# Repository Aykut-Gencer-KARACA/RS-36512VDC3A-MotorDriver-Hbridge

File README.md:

<div align="center">

<br/>

<br/><br/>

**Mikrodenetleyicisiz, tamamen analog PWM ile çalışan çift yönlü motor sürücü.**<br/>
24 V girişten 12.3 V motor barası üretir; hızı bir trimpotla, yönü bir anahtarla ayarlanır.

</div>

## İçindekiler

- [Genel bakış](#-genel-bakış)
- [Öne çıkanlar](#-öne-çıkanlar)
- [Sistem mimarisi](#-sistem-mimarisi)
- [Çalışma prensibi](#-çalışma-prensibi)
- [Donanım](#-donanım)
- [Tasarım hesapları](#-tasarım-hesapları)
- [Şematik](#-şematik)
- [PCB](#-pcb)
- [Malzeme listesi](#-malzeme-listesi)
- [Depo yapısı](#-depo-yapısı)

## ◆ Genel bakış

Bu proje, bir önceki çalışmamda kullandığım **RS-365 serisi 12 V DC / 3 A** motoru **çift yönlü** ve **hız kontrollü** sürmek için tasarlanmış bir H-köprü kartıdır. Güç tarafında 24 V DC girişten **LM2596S-ADJ** ile 12.3 V'luk motor barası üretilir. PWM sinyali mikrodenetleyici olmadan **LM555** ile, yön kararı **CD4081 / CD4069** mantık kapılarıyla verilir; köprüyü iki adet **EG4427** gate sürücü besler.

| Özellik | Değer |
|---|---|
| **Giriş** | 24 V DC · vida klemens (J1) · 2.5 A sigorta (F1) |
| **Motor barası** | 12.3 V · LM2596S-ADJ, R10 1 kΩ / R11 9 kΩ geri besleme |
| **Motor** | RS-365 · 12 V DC · 3 A |
| **Regülatör** | L1 68 µH (ISAT 4.5 A) · D6 4 A Schottky · çıkışta C8, C9 470 µF 35 V |
| **PWM** | LM555 astable · C15 6.8 nF · hesaplanan ≈ 16 kHz · duty ≈ %15 – %92 |
| **Hız ayarı** | RV1 10 kΩ multiturn trimpot |
| **Yön** | SW1 SPDT, orta konumda dur · CD4081 (AND) + CD4069 (NOT) |
| **Gate sürücü** | 2 × EG4427 · MOSFET başına 100 Ω gate direnci |
| **Köprü** | Q2, Q4 P-kanal (üst) · Q3, Q5 N-kanal (alt) · TO-220 · her birine paralel 4 A Schottky |
| **Kart** | 115.65 × 44.48 mm · 4 katmanlı · 1.6 mm |

## ◆ Öne çıkanlar

<table>
<tr>
<td width="50%" valign="top">

**Tamamen analog PWM**<br/>
Frekans ve duty bir LM555 ile üretilir. İki diyot şarj ve deşarj yollarını ayırdığı için trimpot yalnızca duty'yi değiştirir; toplam direnç sabit kaldığından frekans yaklaşık sabittir.

</td>
<td width="50%" valign="top">

**Giriş koruması**<br/>
2.5 A sigorta, P-kanal giriş MOSFET'i (Q1) ve gate'i 12 V zener (D1) ile sınırlanmış koruma devresi. Sigorta 24 V tarafında olduğu için 3 A motor akımı, giriş tarafında yaklaşık 1.8 A'e karşılık gelir (%85 verim varsayımıyla).

</td>
</tr>
<tr>
<td valign="top">

**Gate sürücü ile hızlı anahtarlama**<br/>
Mantık kapıları gate'i doğrudan sürecek akımı veremez. İki EG4427, gate'leri 100 Ω dirençler üzerinden besler; her MOSFET'te 10 kΩ pull-up / pull-down açılış anında gate'i kapalı tutar.

</td>
<td valign="top">

**Her MOSFET'e Schottky diyot**<br/>
D2 – D5 (4 A, SMC), PWM kapalıyken motor akımının dolaşacağı yolu açar ve MOSFET gövde diyotlarını rahatlatır.

</td>
</tr>
</table>

## ◆ Sistem mimarisi

Güç yolu soldan sağa akıyor: 24 V giriş sigortadan, giriş koruma devresinden (Q1, D1) ve LM2596'dan geçip 12.3 V'luk `V_MOTOR` barasına ulaşıyor. Bu baradan iki kol ayrılıyor:

- **Mantık beslemesi** · 10 Ω (R12) ve 470 µF (C11) ile süzülerek LM555, CD4081, CD4069 ve EG4427'leri besler (kesim frekansı ≈ 34 Hz).
- **H-köprü** · MOSFET'ler ve motor doğrudan bu baradan beslenir.

PWM, yön bilgisiyle kapılarda birleştirilir; EG4427'ler sinyali güçlendirip köprünün dört MOSFET'ine iletir.

## ◆ Çalışma prensibi

Köprünün her bacağında bir P-kanal (üst) ve bir N-kanal (alt) MOSFET vardır; motor iki bacağın orta noktaları arasına bağlanır.

- **İleri:** Q2 sabit iletimde, Q5 PWM ile anahtarlanır. Akım `V_MOTOR → Q2 → motor → Q5 → GND` yolunu izler.
- **Geri:** Q4 sabit iletimde, Q3 PWM ile anahtarlanır. Akım motordan ters yönde geçer.
- **Dur:** SW1 orta konumdayken tüm çıkışlar pasiftir.
- **Hız:** Motora uygulanan ortalama gerilim $V_{ort} \approx D \times 12.3\text{ V}$ olur; RV1 duty'yi değiştirir.

Üst kolda P-kanal MOSFET'ler kullanılmıştır: gate'e GND yakın bir gerilim verildiğinde açılırlar, gate'leri pull-up dirençleriyle motor barasına bağlı olduğundan boşta kapalı kalırlar ve böylece üst kol için ayrıca bir bootstrap devresi gerekmez.

## ◆ Donanım

<details open>
<summary><b>Güç girişi ve regülatör</b></summary>
<br/>

| Blok | Parça | Not |
|---|---|---|
| Giriş | J1 vida klemens (MX126-5.0-02P, C5188434; 5.00 mm, 10 A, 300 V) · F1 2010T2.5A250V (C354903; 2.5 A, 300 V DC) | Sigorta 24 V tarafında |
| Giriş koruma MOSFET'i | Q1 (P-kanal, TO-220) · R2 10 kΩ · D1 ZMM12V (C5345999; 11.4 – 12.7 V, 500 mW) | Gate R2 ile GND'ye çekili, zener V<sub>GS</sub>'i sınırlar |
| Regülatör | U3 LM2596S-ADJ | R10 1 kΩ / R11 9 kΩ → 12.3 V |
| Bobin | L1 SMMS0865-680MT · 68 µH (C42443515) | ISAT 4.5 A · Irms 4 A · DCR 180 mΩ · 9 × 8.1 mm |
| Diyot | D6 4 A Schottky (SMC) | Serbest dolaşım |
| Giriş kondansatörleri | C1, C2 470 µF 35 V (şematik değeri) · C4 1 µF | Anahtarlama anındaki ani akımı karşılar. Kütüphane kaydı (LCSC C335982) ROQANG RVT1A471M0607 = 470 µF / **10 V**, 6.3 × 7.7 mm'dir |
| Çıkış kondansatörleri | C8, C9 470 µF 35 V (şematik değeri) · C10 1 µF | Hızlı tepki için seramik, süreğen düşüşler için polarize; C8 / C9 için de aynı kütüphane parçası (10 V) geçerlidir |

</details>

<details>
<summary><b>PWM üretimi — LM555</b></summary>
<br/>

- Astable modda çalışır; C15 = 6.8 nF kondansatör Vcc'nin 1/3 ile 2/3'ü arasında şarj/deşarj olur.
- D7 ve D8 diyotları şarj ve deşarj akımlarını RV1'in iki farklı yarısından geçirir. Şarj yolu: `R16 + RV1(üst) + R15`, deşarj yolu: `RV1(alt) + R15`.
- Toplam direnç RV1'in konumundan bağımsızdır; bu yüzden frekans sabit kalır, yalnızca duty değişir.
- C13 ve C14 besleme / kontrol pini dekuplaj kondansatörleridir.

</details>

<details>
<summary><b>Karar birimi — SW1, CD4081, CD4069</b></summary>
<br/>

- SW1 üç konumlu (orta konumda OFF) bir SPDT anahtardır; seçilen yön hattı 12 V'a çekilirken diğeri R13 / R14 (10 kΩ) ile GND'de tutulur.
- **CD4081** (dörtlü AND) yön bilgisini LM555 PWM çıkışıyla birleştirir.
- **CD4069** (altılı NOT) yön hatlarını tersleyerek üst kol P-kanal MOSFET'lerin (Q2, Q4) gate sinyalini üretir; CD4081 çıkışları ise alt kol (Q3, Q5) sürücüsüne gider.
- Mantık beslemesi (`IC_Input`) 10 Ω + 470 µF ile süzülen 12.3 V barasından gelir; 4000 serisi CMOS bu gerilimde çalışır.

</details>

<details>
<summary><b>Gate sürücü — EG4427</b></summary>
<br/>

- İki entegre, dört MOSFET gate'ini sürer (INA / INB → OUTA / OUTB).
- Her entegrenin beslemesinde 4.7 µF + 100 nF bulunur.
- Çıkışlar 100 Ω (R3, R4, R7, R8) gate dirençleriyle MOSFET'lere gider.
- Üst kol gate'leri 10 kΩ (R1, R9) ile motor barasına, alt kol gate'leri 10 kΩ (R5, R6) ile GND'ye bağlıdır.

</details>

<details>
<summary><b>Motor köprüsü</b></summary>
<br/>

| Ref | Tür | Görev |
|---|---|---|
| Q2, Q4 | P-kanal, TO-220 | Üst kol, yön seçimi |
| Q3, Q5 | N-kanal, TO-220 | Alt kol, PWM |
| D2 – D5 | 4 A Schottky, SMC | Her MOSFET'e paralel serbest dolaşım diyodu |
| M1 | Vida klemens | Motor bağlantısı |

</details>

## ◆ Tasarım hesapları

> Değerler KiCad şematik / PCB dosyalarından (RevA), TI LM2596 (SNVS124G) ve LM555 (SNAS548D) datasheet'lerinden ve EG4427'nin LCSC ürün sayfasından alınmıştır. MOSFET'lerin parça numarası şematikte yazılı olmadığı için MOSFET hesapları gereksinim düzeyindedir; datasheet'te karşılığı olmayan değerler "varsayım" diye işaretlenmiştir.

<details>
<summary><b>Giriş akımı ve sigorta</b></summary>
<br/>

$$P_{OUT} = 12.3\text{ V} \times 3\text{ A} = 36.9\text{ W} \quad\Rightarrow\quad I_{IN} = \frac{36.9\text{ W}}{\eta \times 24\text{ V}} = 1.71\text{ A}\ (\eta = 0.90),\quad 1.81\text{ A}\ (\eta = 0.85)$$

η = %90, LM2596 datasheet'inin 25 V → 12 V, 3 A noktasındaki tipik verimidir (7.7). 2.5 A sigorta bu akımın ≈ 1.4 katıdır; sigortanın sürekli akımda anma değerinin %75'inde (1.9 A) çalıştırılması kuralıyla 1.7 – 1.8 A sınırın içindedir. Motorun kalkış / sıkışma akımı 3 A'i belirgin aşarsa sigorta ve LM2596'nın akım sınırı devreye girer (rotor kilitli akımı bu belgede verilmemiştir).

</details>

<details>
<summary><b>Giriş koruma devresi (Q1, D1, R2)</b></summary>
<br/>

Q1'in gate'i R2 (10 kΩ) ile GND'ye çekilidir; D1 (12 V zener) gate ile drain arasında, gate gerilimini drain gerilimine göre en fazla 12 V aşağıda tutar:

$$V_{GS} \approx -12\text{ V}\ (\text{iletimde}), \qquad I_{R2} = \frac{24 - 12}{10\text{ k}\Omega} = 1.2\text{ mA}, \qquad P_{R2} = P_{D1} = 12\text{ V} \times 1.2\text{ mA} = 14.4\text{ mW}$$

R2 için bu, 0805'in 125 mW değerinin %12'sidir. Q1 üzerindeki iletim kaybı $P = I_{IN}^2 R_{DS(on)}$: 1.8 A ve 50 mΩ için 0.16 W. Q1 için $V_{DS} \ge 40\text{ V}$ (60 V önerilir) gerekir. Başlangıçta drain 0 V iken gate geçici olarak 0 V'ta kaldığından $V_{GS}$ kısa süreliğine −24 V'a ulaşır (zener drain 12 V'u aştıktan sonra iletime geçer); bu nedenle gate–source sınırı ±20 V'tan yüksek bir parça tercih edilmelidir.

**Giriş kondansatörleri (C1, C2):** toplam 940 µF; depolanan enerji $\tfrac{1}{2} C V^2 = \tfrac{1}{2} \cdot 940\ \mu\text{F} \cdot 24^2 = 0.27\text{ J}$. LM2596 datasheet'i RMS akımın $\ge I_{LOAD}/2 = 1.5\text{ A}$ (iki kondansatör için her biri ≥ 0.75 A) ve gerilim değerinin $\approx 1.5 \times V_{IN} = 36\text{ V}$ olmasını ister (9.2.2.2.6); 35 V'luk kondansatör 24 V'ta gerilim değerinin %69'unda çalışır.

**Parça doğrulaması (C1, C2, C8, C9):** şematik değeri 470 µF / 35 V'tur, ancak footprint ve 3B model kütüphanedeki LCSC C335982 kaydından gelir: ROQANG RVT1A471M0607, **470 µF / 10 V**, 6.3 × 7.7 mm, dalgalanma akımı 200 mA @ 120 Hz. 6.3 mm gövdeli SMD kutuda 470 µF yalnızca 6.3 – 10 V'ta bulunur; 470 µF / 35 V standart alüminyum elektrolitikte ≈ 10 × 10 mm veya daha büyük kutu gerektirir. 10 V'luk bu parça 24 V (C1, C2) ve 12.3 V (C8, C9) baralarında kullanılamaz. Ayrıca LM2596 girişindeki RMS akım $I_{RMS} = I_{LOAD}\sqrt{D(1-D)} = 3\sqrt{0.548 \cdot 0.452} = 1.49\text{ A}$'dir; iki kondansatörün toplam 0.4 A'lik dalgalanma akımı bunun çok altındadır. 35 V'luk gerçek kondansatörler için footprint değiştirilmelidir.

**C11 (470 µF / 50 V):** footprint 0603 (1.6 × 0.8 mm) olarak atanmıştır; bu değerde bir kondansatör 0603 kılıfta bulunmaz, footprint gerçek parçaya göre düzeltilmelidir.

</details>

<details>
<summary><b>Çıkış gerilimi (12.3 V)</b></summary>
<br/>

$$V_{OUT} = V_{REF} \times \left(1 + \frac{R_{11}}{R_{10}}\right) = 1.23\text{ V} \times \left(1 + \frac{9\text{ k}\Omega}{1\text{ k}\Omega}\right) = 12.3\text{ V}$$

R10 = 1 kΩ, datasheet'in 240 Ω – 1.5 kΩ aralığındadır. Referans toleransıyla (1.193 – 1.267 V) çıkış 11.93 – 12.67 V arasında olabilir (≈ ±%3).

</details>

<details>
<summary><b>Bobin akımı ve akım sınırı</b></summary>
<br/>

Datasheet'in duty ifadesi (Denklem 8; $V_{SAT} = 1.16\text{ V}$, $V_D = 0.5\text{ V}$), 150 kHz ve $L = 68\ \mu\text{H}$ için:

$$D = \frac{12.3 + 0.5}{24 - 1.16 + 0.5} = 0.548, \qquad \Delta I_L = \frac{(24 - 1.16 - 12.3) \times 0.548}{150\text{ kHz} \times 68\ \mu\text{H}} = 0.57\text{ A}$$

$$I_{pk} = 3 + \frac{0.57}{2} = 3.28\text{ A}, \qquad E \cdot T = 38.5\text{ V}\cdot\mu\text{s}$$

Tepe akım, bobinin ISAT değerinin (4.5 A) %73'üdür.

Yük akımı $\Delta I_L / 2 = 0.28\text{ A}$'in altına düşerse regülatör süreksiz moda geçer. LM2596'nın akım sınırı tipik 4.5 A, en az 3.6 A olduğundan sürekli ortalama yük akımı üst sınırı $I_{CL} - \Delta I_L/2 = 3.3\text{ A}$ (en kötü) – 4.2 A (tipik) olur.

</details>

<details>
<summary><b>Serbest dolaşım diyodu (D6) ve çıkış kondansatörleri</b></summary>
<br/>

D6 için datasheet kuralları (9.2.2.2.5): akım ≥ 1.3 × 3 A = 3.9 A (4 A'lik diyot sağlar), ters gerilim ≥ 1.25 × 24 V = 30 V (şematikte yalnızca "4A Schottky" yazılıdır). Normal çalışmada $I_D = 3 \times (1 - 0.548) = 1.35\text{ A}$, $P_D = 0.5 \times 1.35 = 0.68\text{ W}$.

Çıkış kondansatörü için datasheet 82 – 820 µF aralığını ve $\ge 1.5 \times V_{OUT}$ gerilimi ister (9.2.2.2.3). Kartta C8 + C9 = 940 µF'tır (35 V, 18.5 V kuralını sağlar) ve ayrıca R12 üzerinden C11 (470 µF) bağlıdır:

$$f_0 = \frac{1}{2\pi\sqrt{68\ \mu\text{H} \times 940\ \mu\text{F}}} \approx 630\text{ Hz}$$

Çıkış 10 V'un üzerinde olduğundan datasheet $C_{FF} = 1/(31 \cdot 10^3 \cdot R_{11}) \approx 3.6\text{ nF}$ önerir (Tablo 9-6: 12 V için 1 nF); kartta yoktur.

</details>

<details>
<summary><b>LM2596 güç kaybı ve ısıl kontrol</b></summary>
<br/>

İletim modeli: $P_{IC} = 1.16 \times 3 \times 0.548 + 24 \times 5\text{ mA} = 2.03\text{ W}$. Bütçe yöntemi: datasheet'in tipik %90 verimiyle toplam kayıp $36.9 / 0.9 - 36.9 = 4.1\text{ W}$; D6'nın 0.68 W'ı ve L1'in bakır kaybı $I^2 \times DCR = 3^2 \times 0.18\ \Omega = 1.62\text{ W}$ (SMMS0865-680MT, DCR 180 mΩ; LCSC C42443515) düşülürse entegreye $4.1 - 0.68 - 1.62 = 1.80\text{ W}$ kalır; iki yöntem birbirine yakındır. Kart alanı $115.65 \times 44.48 = 5144\text{ mm}^2 \approx 7.97\text{ in}^2$ (4 katman); R<sub>θJA</sub>'nın 20 – 30 °C/W olacağı varsayıldı (datasheet 7.4: 3 in² çift yüzlü → 20, 2.5 in² tek yüzlü → 30 °C/W):

| P<sub>IC</sub> | R<sub>θJA</sub> = 20 °C/W | R<sub>θJA</sub> = 30 °C/W |
|---|---|---|
| 1.80 W (bütçe) | T<sub>J</sub> = 76 °C | T<sub>J</sub> = 94 °C |
| 2.03 W (iletim modeli) | T<sub>J</sub> = 81 °C | T<sub>J</sub> = 101 °C |

İşletme sıcaklığı üst sınırı 125 °C'dir (7.3); her iki yöntemde de ≤ 101 °C'tir. L1 bobininin tam yükteki 1.62 W'lık kaybı (Irms 4 A, sınırın %75'inde çalışır) ayrıca karta ısı verir.

</details>

<details>
<summary><b>PWM frekansı ve duty aralığı (LM555)</b></summary>
<br/>

D7 / D8 şarj ve deşarj yollarını ayırır: şarj $R_{16} + R_a + R_{15}$, deşarj $R_b + R_{15}$ üzerinden ($R_a + R_b = R_{RV1} = 10\text{ k}\Omega$). Datasheet formülleri (7.4.2):

$$t_H = 0.693\,(R_{16} + R_a + R_{15})\,C_{15}, \qquad t_L = 0.693\,(R_b + R_{15})\,C_{15}$$

$$T = 0.693\,(R_{16} + R_{RV1} + 2R_{15})\,C_{15} = 0.693 \times 13\text{ k}\Omega \times 6.8\text{ nF} = 61.3\ \mu\text{s} \;\Rightarrow\; f \approx 16.3\text{ kHz}$$

$$D_{min} = \frac{R_{16} + R_{15}}{R_{16} + R_{RV1} + 2R_{15}} = \frac{2}{13} = 15\%, \qquad D_{max} = \frac{12}{13} = 92\%$$

Frekans RV1'in konumundan bağımsızdır. Diyot düşümü ($V_F = 0.6\text{ V}$, varsayım) dahil edildiğinde ($V_{CC} = 12.3\text{ V}$; kondansatör $V_{CC}/3$ ile $2V_{CC}/3$ arasında):

| R<sub>a</sub> | 0 | 2.5 kΩ | 5 kΩ | 7.5 kΩ | 10 kΩ |
|---|---|---|---|---|---|
| D (ideal) | %15 | %35 | %54 | %73 | %92 |
| f (V<sub>F</sub> = 0.6 V) | 17.4 kHz | 16.7 kHz | 16.0 kHz | 15.4 kHz | 14.8 kHz |
| D (V<sub>F</sub> = 0.6 V) | %18 | %40 | %59 | %77 | %94 |

LM555 astable başlangıç doğruluğu %2.25'tir (6.5). Deşarj sırasında pin 7 yaklaşık 0.15 V'a iner ve R16'dan $(12.3 - 0.15)/1\text{ k}\Omega = 12.2\text{ mA}$ akar (anlık 148 mW); ortalama güç $148\text{ mW} \times (1 - D)$: D ≈ %18'de 121 mW, D ≈ %94'te 9 mW. 0805 direncin anma gücü 125 mW'tır, yani en düşük duty'de R16 anma gücünün %97'sini harcar.

</details>

<details>
<summary><b>Motora uygulanan ortalama gerilim</b></summary>
<br/>

$$V_{avg} \approx D \times 12.3\text{ V}:\qquad D = 15\% \Rightarrow 1.8\text{ V},\quad 25\% \Rightarrow 3.1\text{ V},\quad 50\% \Rightarrow 6.2\text{ V},\quad 75\% \Rightarrow 9.2\text{ V},\quad 92\% \Rightarrow 11.3\text{ V}$$

</details>

<details>
<summary><b>Mantık beslemesi filtresi</b></summary>
<br/>

$$f_c = \frac{1}{2\pi \times R_{12} \times C_{11}} = \frac{1}{2\pi \times 10\ \Omega \times 470\ \mu\text{F}} \approx 34\text{ Hz}$$

Besleme akımı yaklaşık 17 – 20 mA'dir (LM555 ≈ 8 mA, R16 ortalama ≈ 6 mA, pull-up / pull-down'lar 1 – 2.5 mA, gate akımları); R12 üzerindeki düşüm en fazla $20\text{ mA} \times 10\ \Omega = 0.2\text{ V}$'tur ve mantık beslemesi ≈ 12.1 V olur. LM555 için önerilen aralık 4.5 – 16 V'tur.

</details>

<details>
<summary><b>Gate sürücü (EG4427)</b></summary>
<br/>

EG4427 (LCSC C2929102): 3 – 20 V besleme, 1.5 A tepe akım, t<sub>pHL</sub> = 60 ns / t<sub>pLH</sub> = 80 ns. Gate dirençleri 100 Ω olduğundan:

$$I_{pk} = \frac{V_{DD}}{R_g} = \frac{12.3\text{ V}}{100\ \Omega} = 123\text{ mA} \ll 1.5\text{ A}, \qquad R_{g,min} = \frac{12.3\text{ V}}{1.5\text{ A}} = 8.2\ \Omega$$

Gate dolma süresi $t \approx Q_g / I_{pk}$ ve ortalama gate gücü $P = Q_g V_{DD} f$ ($f = 16.3\text{ kHz}$; Q<sub>g</sub> örnek değerlerdir):

| Q<sub>g</sub> (örnek) | 20 nC | 40 nC | 60 nC |
|---|---|---|---|
| Dolma süresi | 163 ns | 325 ns | 488 ns |
| Ortalama gate gücü | 4.0 mW | 8.0 mW | 12.0 mW |

Hepsi 61 µs'lik PWM periyodunun %1'inden küçüktür. 4.7 µF besleme kondansatöründe bir anahtarlamada gerilim düşümü $40\text{ nC} / 4.7\ \mu\text{F} = 8.5\text{ mV}$'tur. 10 kΩ pull-up / pull-down'lardan iletimdeki bir gate için $12.3 / 10\text{ k}\Omega = 1.23\text{ mA}$ akar.

**Sürücü etkinleştirme ve mantık seviyeleri.** EG4427'nin 8 numaralı pini SD (shutdown) girişidir ve aktif-yüksektir (LCSC / EGmicro: "SD high disables outputs"; dahili 100 kΩ pull-down). Kartta SD pini GND'ye bağlıdır, yani sürücüler etkindir. Giriş eşikleri $V_{IH} = 2.5\text{ V}$, $V_{IL} = 1\text{ V}$'tur. CD4081BE (HGSEMI, C507156) ve CD4069 (Slkor, C3041279) 3 – 15 V aralığında çalışır; 12.1 V beslemede CMOS giriş eşiği $V_{IH} \approx 8.7\text{ V}$ (10 V'ta 7 V, 15 V'ta 11 V arasında doğrusal). LM555 çıkışı 100 mA'de en az $V_{CC} - 2.25\text{ V} \approx 9.9\text{ V}$ verdiğinden (CMOS yükünde daha yüksektir) gürültü payı ≥ 1.2 V'tur; LM555 alçak çıkışı ≤ 0.25 V'tur.

</details>

<details>
<summary><b>MOSFET ve Schottky diyot gereksinimleri</b></summary>
<br/>

| Parametre | Gereksinim | Hesap |
|---|---|---|
| V<sub>DS</sub> (Q2 – Q5) | ≥ 30 V | $2 \times 12.3\text{ V} \approx 25\text{ V}$ |
| V<sub>DS</sub> (Q1) | ≥ 40 V (60 V önerilir) | 24 V giriş + sıçramalar |
| I<sub>D</sub> | ≥ 9 A | $3 \times 3\text{ A}$ (ön eleme) |
| R<sub>DS(on)</sub> @ 12 V | ≤ 100 mΩ | 3 A'de $I^2 R \le 0.9\text{ W}$ |
| V<sub>GS(th)</sub> | ≤ 4 V | 12 V sürüşte tam iletim |

3 A'de iletim kaybı 30 mΩ için 0.27 W, 50 mΩ için 0.45 W, 100 mΩ için 0.90 W'tır; alt kolda PWM olduğundan ortalama kayıp D katıdır. D2 – D5 serbest dolaşım diyotlarının kaybı $P = V_F\,I\,(1 - D)$ ($V_F = 0.5\text{ V}$, 3 A varsayımı): D = %15'te 1.28 W, %50'de 0.75 W, %92'de 0.12 W.

</details>

## ◆ Şematik

Şematik beş bölüme ayrılmıştır: 24 V → 12 V regülatör, LM555 zamanlayıcı, karar birimi, gate sürücüler ve motor köprüsü.

## ◆ PCB

<table>
<tr>
<td width="50%"></td>
<td width="50%"></td>
</tr>
<tr>
<td align="center"><sub>Hero görünüm (sol önden, 3/4)</sub></td>
<td align="center"><sub>Üstten görünüm · 115.65 × 44.48 mm</sub></td>
</tr>
</table>

Kart 4 katmanlı, 1.6 mm kalınlıktadır. Görseller [DRC Analyzer](https://github.com/Aykut-Gencer-KARACA/DRC-Analyzer) ile projenin 3B modelinden üretilmiştir; tam çözünürlüklü dosyalar `KiCad Project/Renders/` klasöründedir. L1'in 3B modeli olmadığı için bobin gövdesi görünmez; yalnızca lehim padleri ve kılıf çerçevesi çıkar.

## ◆ Malzeme listesi

<details>
<summary><b>Ana bileşenler</b> (tam liste için tıklayın)</summary>
<br/>

| Ref | Açıklama | Parça | Adet | Kılıf |
|---|---|---|:-:|---|
| U3 | Buck regülatör | LM2596S-ADJ | 1 | TO-263-5 |
| U6 | PWM zamanlayıcı | LM555 | 1 | SOIC-8 |
| U4 | Dörtlü AND | CD4081BE (LCSC C507156) | 1 | DIP-14 |
| U5 | Altılı NOT | CD4069 (LCSC C3041279) | 1 | SOP-14 |
| U1, U2 | Gate sürücü | EG4427 (LCSC C2929102) | 2 | SOP-8 |
| Q1 | Giriş koruma MOSFET'i (P-kanal) | — | 1 | TO-220 |
| Q2, Q4 | Köprü üst kol (P-kanal) | — | 2 | TO-220 |
| Q3, Q5 | Köprü alt kol (N-kanal) | — | 2 | TO-220 |
| D2 – D5 | Köprü Schottky diyotları | 4 A | 4 | SMC |
| D6 | Buck Schottky diyodu | 4 A | 1 | SMC |
| D1 | Zener diyot | ZMM12V · 12 V, 500 mW (LCSC C5345999) | 1 | LL-34 |
| D7, D8 | PWM yönlendirme diyotları | — | 2 | SOD-523 |
| F1 | Sigorta | 2010T2.5A250V · 2.5 A, 300 V DC (LCSC C354903) | 1 | THT, 5.08 mm |
| L1 | Buck bobini | SMMS0865-680MT · 68 µH, Irms 4 A, ISAT 4.5 A, DCR 180 mΩ (LCSC C42443515) | 1 | SMD 9.0 × 8.1 |
| SW1 | Yön anahtarı | MT-0-103-A101-M200-RS · SPDT, orta konum OFF, 5 A / 125 V AC (LCSC C1788493) | 1 | THT |
| RV1 | Hız trimpotu | 10 kΩ multiturn (Bourns 3296W) | 1 | THT |
| J1, M1 | Giriş ve motor klemensi | MX126-5.0-02P-GN01 · 2 kutuplu, 5.00 mm, 10 A, 300 V (LCSC C5188434) | 2 | THT |

**Kondansatörler (16)** (şematik değerleri; C1, C2, C8, C9 için kütüphane parçası ROQANG RVT1A471M0607 = 470 µF / 10 V, LCSC C335982; C11 470 µF için footprint 0603): 4 × 470 µF 35 V · 1 × 470 µF 50 V · 2 × 4.7 µF 50 V · 2 × 1 µF 50 V · 5 × 100 nF 50 V · 1 × 100 nF 16 V · 1 × 6.8 nF 16 V.

**Dirençler (16, 0805 / 0603):** 7 × 10 kΩ · 4 × 100 Ω · 3 × 1 kΩ · 1 × 9 kΩ · 1 × 10 Ω.

**Sistem:** RS-365 12 V DC motor · 24 V DC kaynak.

</details>

## ◆ Depo yapısı

```text
RS-36512VDC3A-MotorDriver-Hbridge/
├─ KiCad Project/                  KiCad projesi (güncel sürüm: RevA)
│  ├─ RS36512VDCDriver.kicad_pro   KiCad proje dosyası
│  ├─ RS36512VDCDriver.kicad_sch   Şematik
│  ├─ RS36512VDCDriver.kicad_pcb   PCB
│  ├─ Layer_Images/                Katman görüntüleri, şematik PDF, 3D .glb
│  ├─ Renders/                     Yüksek çözünürlüklü PCB render'ı
│  ├─ EasyEDA.kicad_sym            Sembol kütüphanesi
│  ├─ EasyEDA.pretty/              Footprint'ler
│  └─ EasyEDA.3dshapes/            3D modeller
├─ assets/                         README görselleri
└─ README.md
```

Projeyi açmak için KiCad'de `KiCad Project/RS36512VDCDriver.kicad_pro` dosyasını açın. Revizyon bilgisi şemanın ve PCB'nin başlık bloğundadır.

<br/>

<div align="center">

<br/>
<sub>LM2596 · LM555 · CD4081 · CD4069 · EG4427</sub>
</div>

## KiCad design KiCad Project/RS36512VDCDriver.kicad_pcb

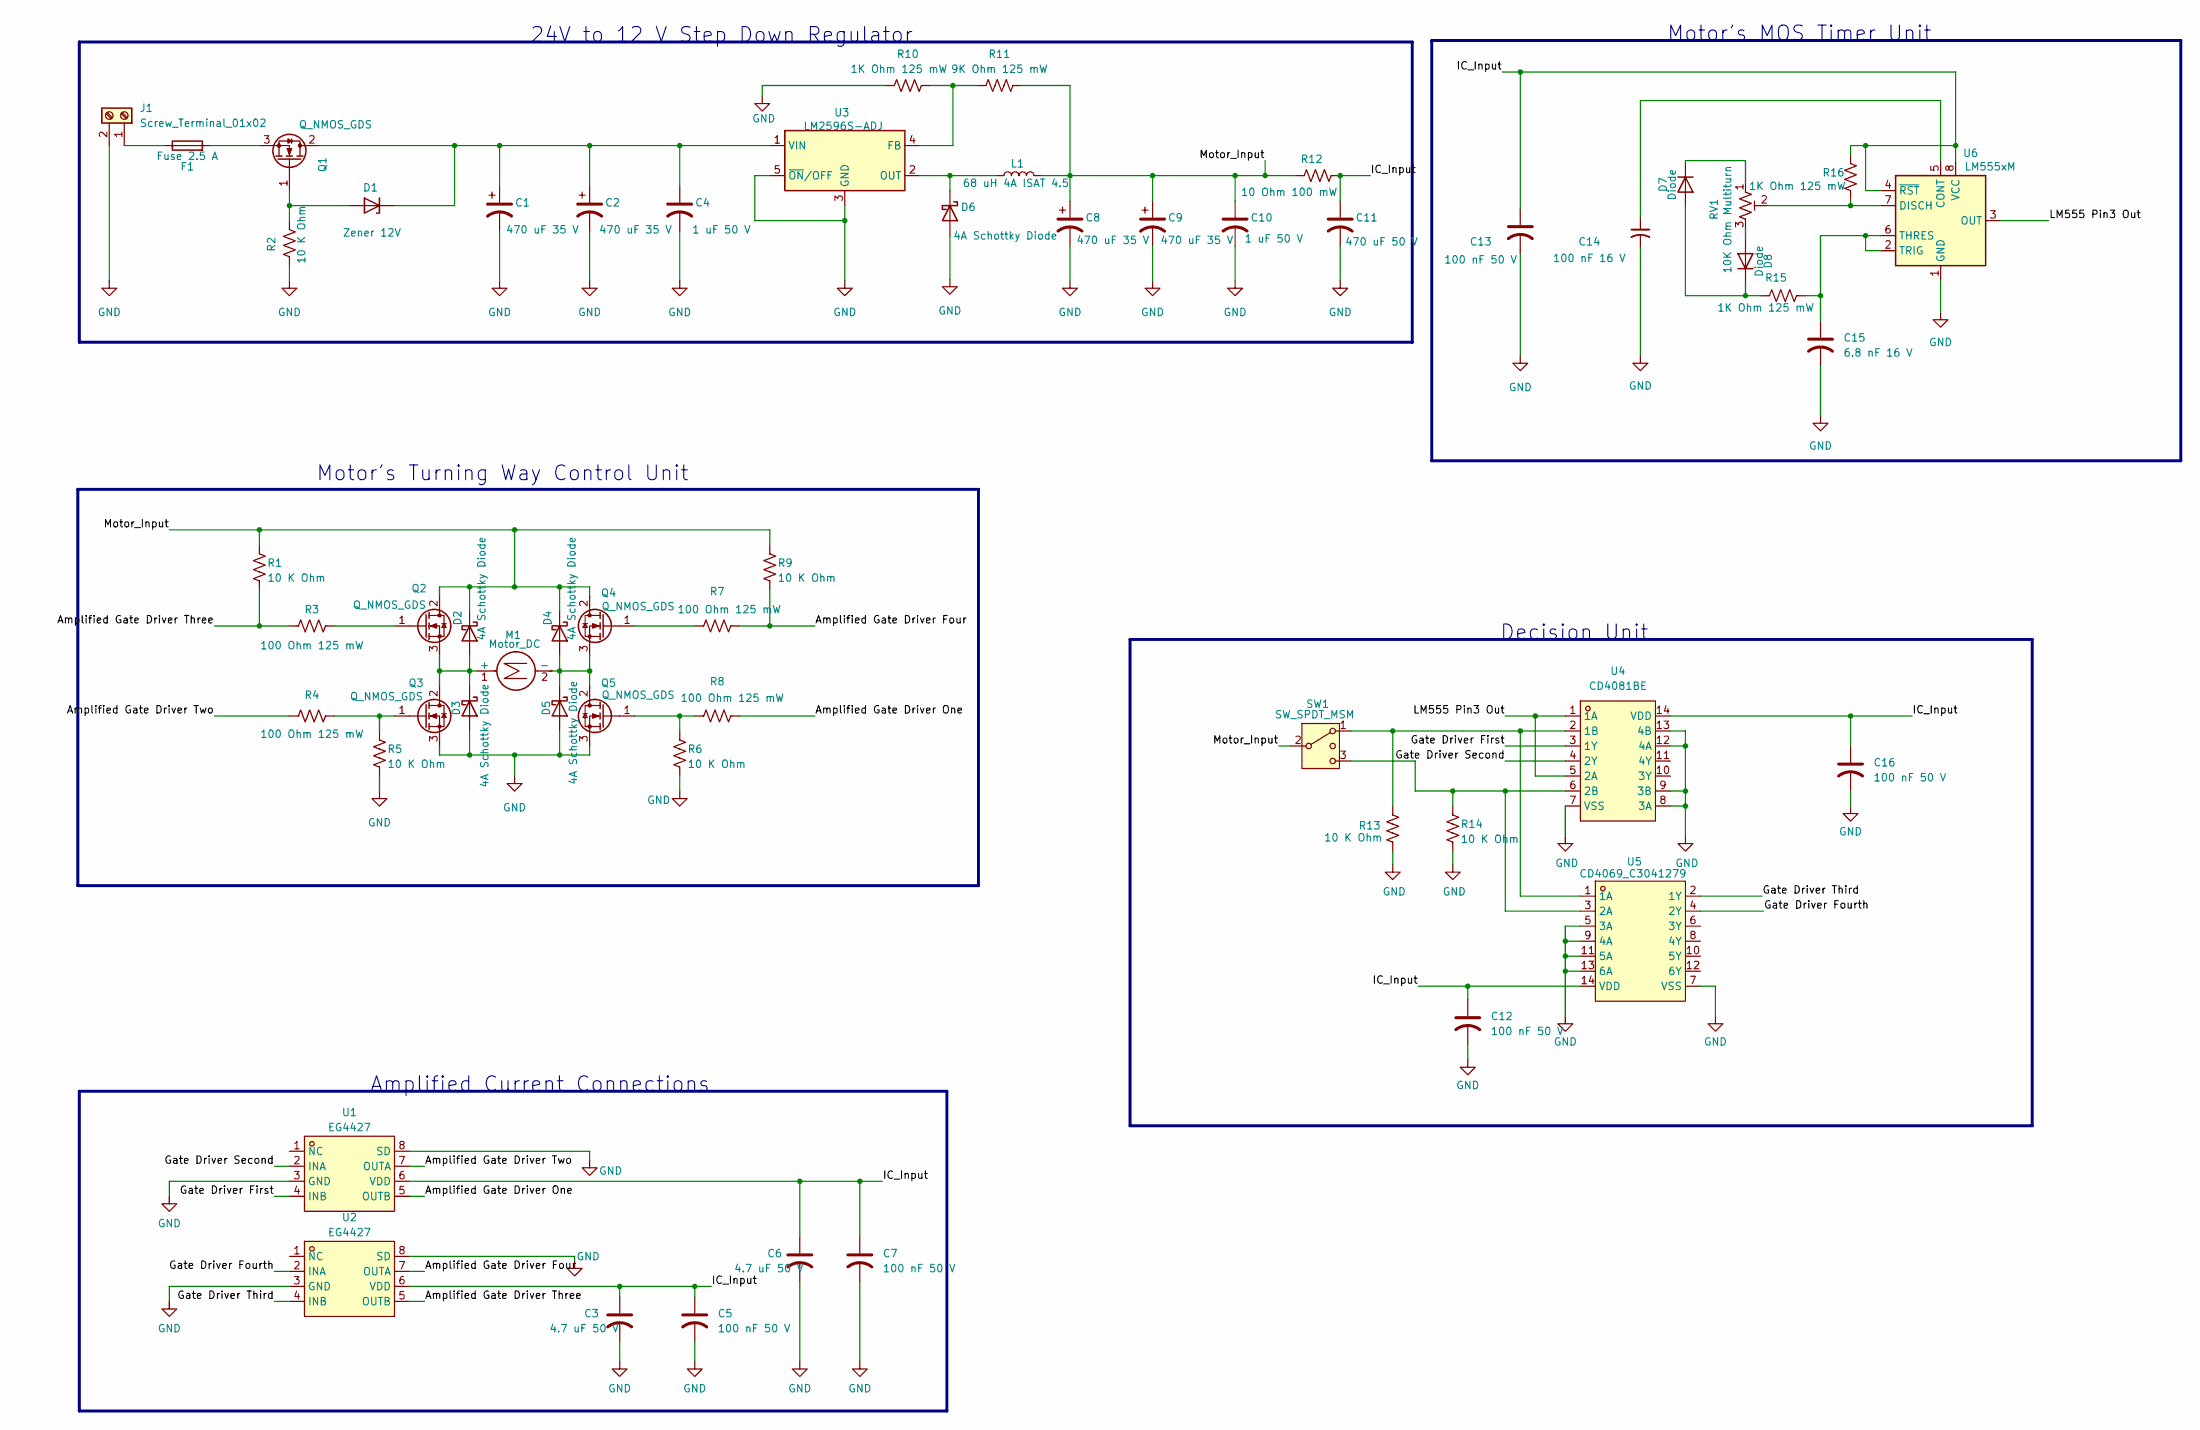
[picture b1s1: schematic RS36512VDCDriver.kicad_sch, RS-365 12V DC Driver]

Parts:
C1, C2, C8, C9: 470 uF 35 V; CAP-SMD_BD6.3-L6.6-W6.6-FD
C3, C6: 4.7 uF 50 V; C_0805_2012Metric
C4, C10: 1 uF 50 V; C_0603_1608Metric
C5, C7, C12, C13, C16: 100 nF 50 V; C_0603_1608Metric
C11: 470 uF 50 V; C_0603_1608Metric
C14: 100 nF 16 V; C_0402_1005Metric
C15: 6.8 nF 16 V; C_0201_0603Metric
D1: Zener 12V; LL-34_L3.5-W1.5-RD-2
D2, D3, D4, D5, D6: 4A Schottky Diode; D_SMC
D7, D8: Diode; D_SOD-523
F1: Fuse 2.5 A; FUSE-TH_L8.5-W4.0-P5.08-D0.6
J1: Screw_Terminal_01x02; CONN-TH_2P-P5.00_MX126-5.0-GN01-02P-CU-S-A
L1: 68 uH 4A ISAT 4.5; IND-SMD_L9.0-W8.1
M1: Motor_DC; CONN-TH_2P-P5.00_MX126-5.0-GN01-02P-CU-S-A
Q1, Q2, Q3, Q4, Q5: Q_NMOS_GDS; TO-220-3_Vertical
R1, R2, R5, R6, R9, R13, R14: 10 K Ohm; R_0805_2012Metric
R3, R4, R7, R8: 100 Ohm 125 mW; R_0805_2012Metric
R10, R15, R16: 1K Ohm 125 mW; R_0805_2012Metric
R11: 9K Ohm 125 mW; R_0805_2012Metric
R12: 10 Ohm 100 mW; R_0603_1608Metric
RV1: 10K Ohm Multiturn; Potentiometer_Bourns_3296W_Vertical
SW1: SW_SPDT_MSM; SW-TH_MT-0-103-A101-M200-RS
U1, U2: EG4427; SOP-8_L4.9-W3.9-P1.27-LS6.0-BL; MPN EG4427; LCSC Part C2929102
U3: LM2596S-ADJ; TO-263-5_TabPin3
U4: CD4081BE; DIP-14_L19.4-W6.4-P2.54-LS7.6-BL; MPN CD4081BE; LCSC Part C507156
U5: CD4069_C3041279; SOP-14_L8.8-W3.9-P1.27-LS6.0-BL; MPN CD4069; LCSC Part C3041279
U6: LM555xM; SOIC-8_3.9x4.9mm_P1.27mm

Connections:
/Amplified Gate Driver Four: R7.2, R9.2, U2.7 (OUTA)
/Amplified Gate Driver One: R8.2, U1.5 (OUTB)
/Amplified Gate Driver Three: R1.2, R3.1, U2.5 (OUTB)
/Amplified Gate Driver Two: R4.1, U1.7 (OUTA)
/Gate Driver First: U1.4 (INB), U4.3 (1Y)
/Gate Driver Fourth: U2.2 (INA), U5.4 (2Y)
/Gate Driver Second: U1.2 (INA), U4.4 (2Y)
/Gate Driver Third: U2.4 (INB), U5.2 (1Y)
/IC_Input: C3.1, C5.1, C6.1, C7.1, C11.1, C12.1, C13.1, C16.1, R12.2, R16.2, U1.6 (VDD), U2.6 (VDD), U4.14 (VDD), U5.14 (VDD), U6.4 (~RST), U6.8 (VCC)
/LM555 Pin3 Out: U4.1 (1A), U4.5 (2A), U6.3 (OUT)
/Motor_Input: C8.1, C9.1, C10.1, D2.1 (K), D4.1 (K), L1.2, Q2.2 (D), Q4.2 (D), R1.1, R9.1, R11.2, R12.1, SW1.2 (3)
GND: C1.2, C2.2, C3.2, C4.2, C5.2, C6.2, C7.2, C8.2, C9.2, C10.2, C11.2, C12.2, C13.2, C14.2, C15.2, C16.2, D3.2 (A), D5.2 (A), D6.2 (A), J1.2, Q3.3 (S), Q5.3 (S), R2.2, R5.2, R6.2, R10.1, R13.2, R14.2, U1.3 (GND), U1.8 (SD), U2.3 (GND), U2.8 (SD), U3.3 (GND), U3.5 (~ON/OFF), U4.7 (VSS), U4.8 (3A), U4.9 (3B), U4.12 (4A), U4.13 (4B), U5.5 (3A), U5.7 (VSS), U5.9 (4A), U5.11 (5A), U5.13 (6A), U6.1 (GND)
unnamed: D1.2 (A), Q1.1 (G), R2.1
unnamed: C1.1, C2.1, C4.1, D1.1 (K), Q1.2 (D), U3.1 (VIN)
unnamed: D2.2 (A), D3.1 (K), M1.1 (+), Q2.3 (S), Q3.2 (D)
unnamed: D4.2 (A), D5.1 (K), M1.2 (-), Q4.3 (S), Q5.2 (D)
unnamed: D6.1 (K), L1.1, U3.2 (OUT)
unnamed: D7.2 (A), D8.1 (K), R15.2
unnamed: D7.1 (K), RV1.1
unnamed: D8.2 (A), RV1.3
unnamed: F1.1, J1.1
unnamed: F1.2, Q1.3 (S)
unnamed: Q2.1 (G), R3.2
unnamed: Q3.1 (G), R4.2, R5.1
unnamed: Q4.1 (G), R7.1
unnamed: Q5.1 (G), R6.1, R8.1
unnamed: R14.1, SW1.3 (4), U4.6 (2B), U5.3 (2A)
unnamed: R10.2, R11.1, U3.4 (FB)
unnamed: R13.1, SW1.1, U4.2 (1B), U5.1 (1A)
unnamed: C14.1, U6.5 (CONT)
unnamed: R16.1, RV1.2, U6.7 (DISCH)
unnamed: C15.1, R15.1, U6.2 (TRIG), U6.6 (THRES)

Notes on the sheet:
Decision Unit
Motor's Turning Way Control Unit
24V to 12 V Step Down Regulator
Amplified Current Connections
Motor's MOS Timer Unit

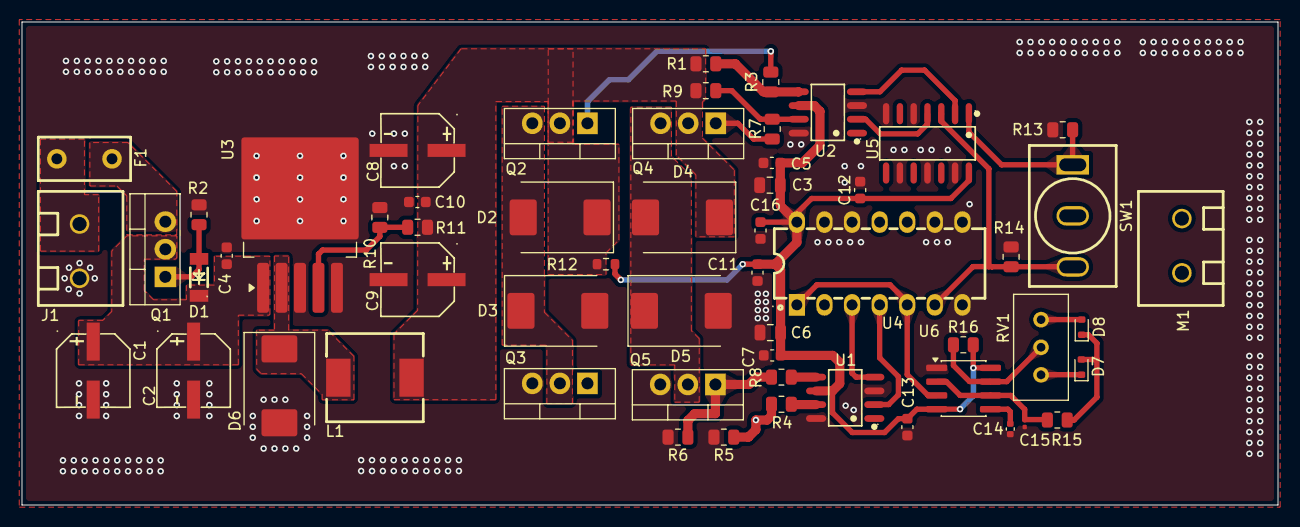
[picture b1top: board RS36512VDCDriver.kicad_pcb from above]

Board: 4 copper layers, 115.7 x 44.5 mm, 57 parts (0 on the bottom side), 32 nets.
